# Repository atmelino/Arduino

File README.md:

# Arduino

Contents:

<h2>MPPT Arduino</h2>

http://www.home-automation-community.com/arduino-low-power-how-to-run-atmega328p-for-a-year-on-coin-cell-battery/

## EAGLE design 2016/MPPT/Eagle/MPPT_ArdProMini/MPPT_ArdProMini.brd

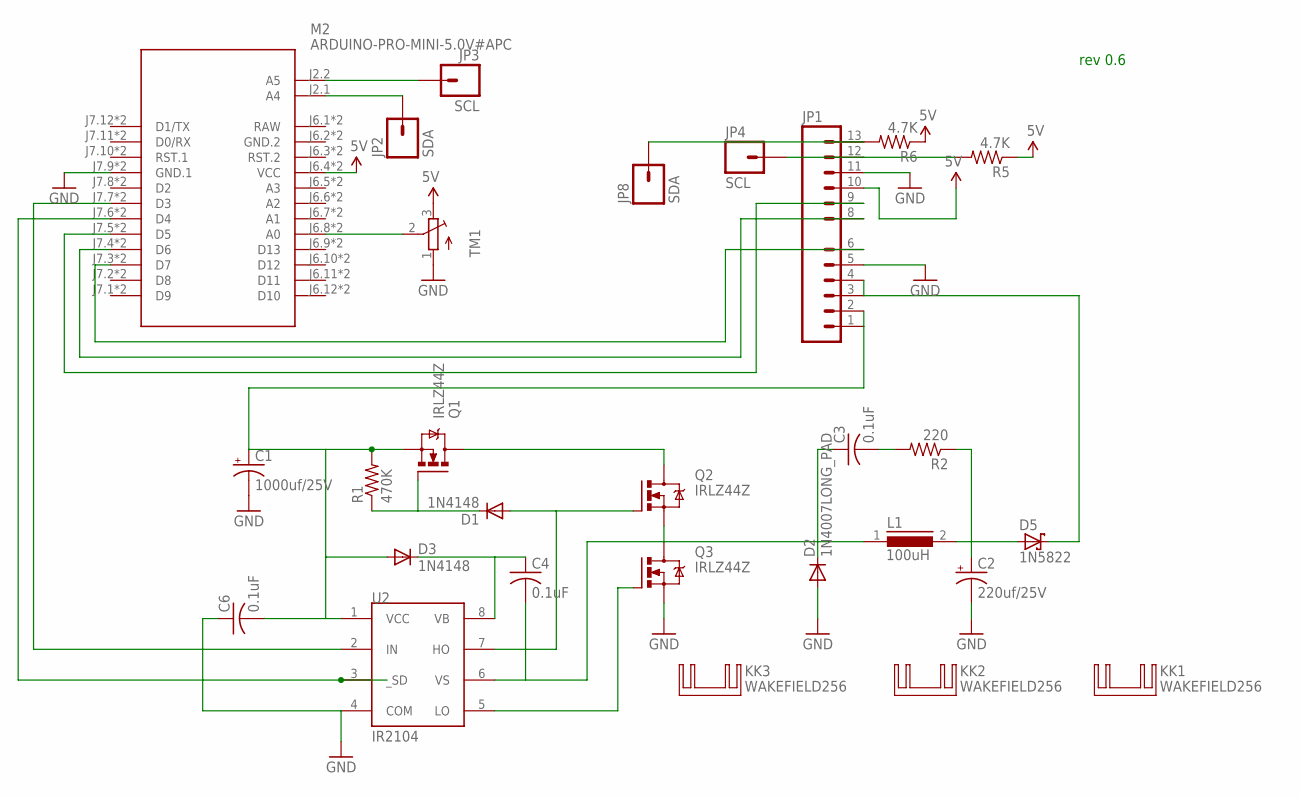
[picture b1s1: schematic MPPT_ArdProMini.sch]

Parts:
C1: 1000uf/25V; CPOL-RADIAL-1000UF-25V-KIT
C2: 220uf/25V; CPOL-RADIAL-1000UF-25V-KIT
C3: 0.1uF; C025-030X050
C4: 0.1uF; C050-030X075
C6: 0.1uF; C075-042X103
D1, D3: 1N4148; DO35-10
D2: 1N4007LONG_PAD; DO35-7
D5: 1N5822; DO201T15
JP1: M06_PLUS_06MPPT; M06_PLUS_06_MPPT
JP2, JP8: SDA; 1X01_OCT
JP3, JP4: SCL; 1X01_OCT
KK1, KK2, KK3: WAKEFIELD256; WAKEFIELD265
L1: 100uH; SFT830D
M2: ARDUINO-PRO-MINI-5.0V#APC; ARDUINO-PRO-MINI_EXTRAPADS
Q1, Q2, Q3: IRLZ44Z; TO220V
R1: 470K; 0204/7
R2: 220; 0204/7
R5, R6: 4.7K; 0204/7
TM1: TRIMPOT; TRIM-3386U
U2: IR2104; DIL08

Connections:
5V: JP1.10, M2.J6.4 (VCC), M2.J6.4_LONG (VCC), R5.1, R6.1, TM1.3 (E)
GND: C1.-, C2.-, C6.1, D2.A, JP1.5, JP1.11, M2.J7.9 (GND.1), M2.J7.9_LONG (GND.1), Q3.S, TM1.1 (A), U2.4 (COM)
GND.2: M2.J6.2 (GND.2), M2.J6.2_LONG (GND.2)
unnamed: M2.J6.8 (A0), M2.J6.8_LONG (A0), TM1.2 (S)
unnamed: JP1.12, JP4.1, R5.2
unnamed: Q3.G, U2.5 (LO)
unnamed: D1.C, Q1.G, R1.1
unnamed: JP1.9, M2.J7.5 (D5), M2.J7.5_LONG (D5)
unnamed: D5.C, JP1.3, JP1.4
unnamed: Q1.D, Q2.D
unnamed: JP1.8, M2.J7.4 (D6), M2.J7.4_LONG (D6)
unnamed: JP1.6, M2.J7.3 (D7), M2.J7.3_LONG (D7)
unnamed: C3.2, R2.2
unnamed: JP2.1, M2.J2.1 (A4)
unnamed: C3.1, C4.2, D2.C, L1.1, Q2.S, Q3.D, U2.6 (VS)
unnamed: C2.+, D5.A, L1.2, R2.1
unnamed: JP3.1, M2.J2.2 (A5)
unnamed: M2.J7.7 (D3), M2.J7.7_LONG (D3), U2.2 (IN)
unnamed: M2.J7.6 (D4), M2.J7.6_LONG (D4), U2.3 (_SD)
unnamed: D1.A, Q2.G, U2.7 (HO)
RAW: M2.J6.1 (RAW), M2.J6.1_LONG (RAW)
SDA: JP1.13, JP8.1, R6.2
VB: C4.1, D3.C, U2.8 (VB)
VCC: C1.+, C6.2, D3.A, JP1.1, JP1.2, Q1.S, R1.2, U2.1 (VCC)

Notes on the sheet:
rev 0.6

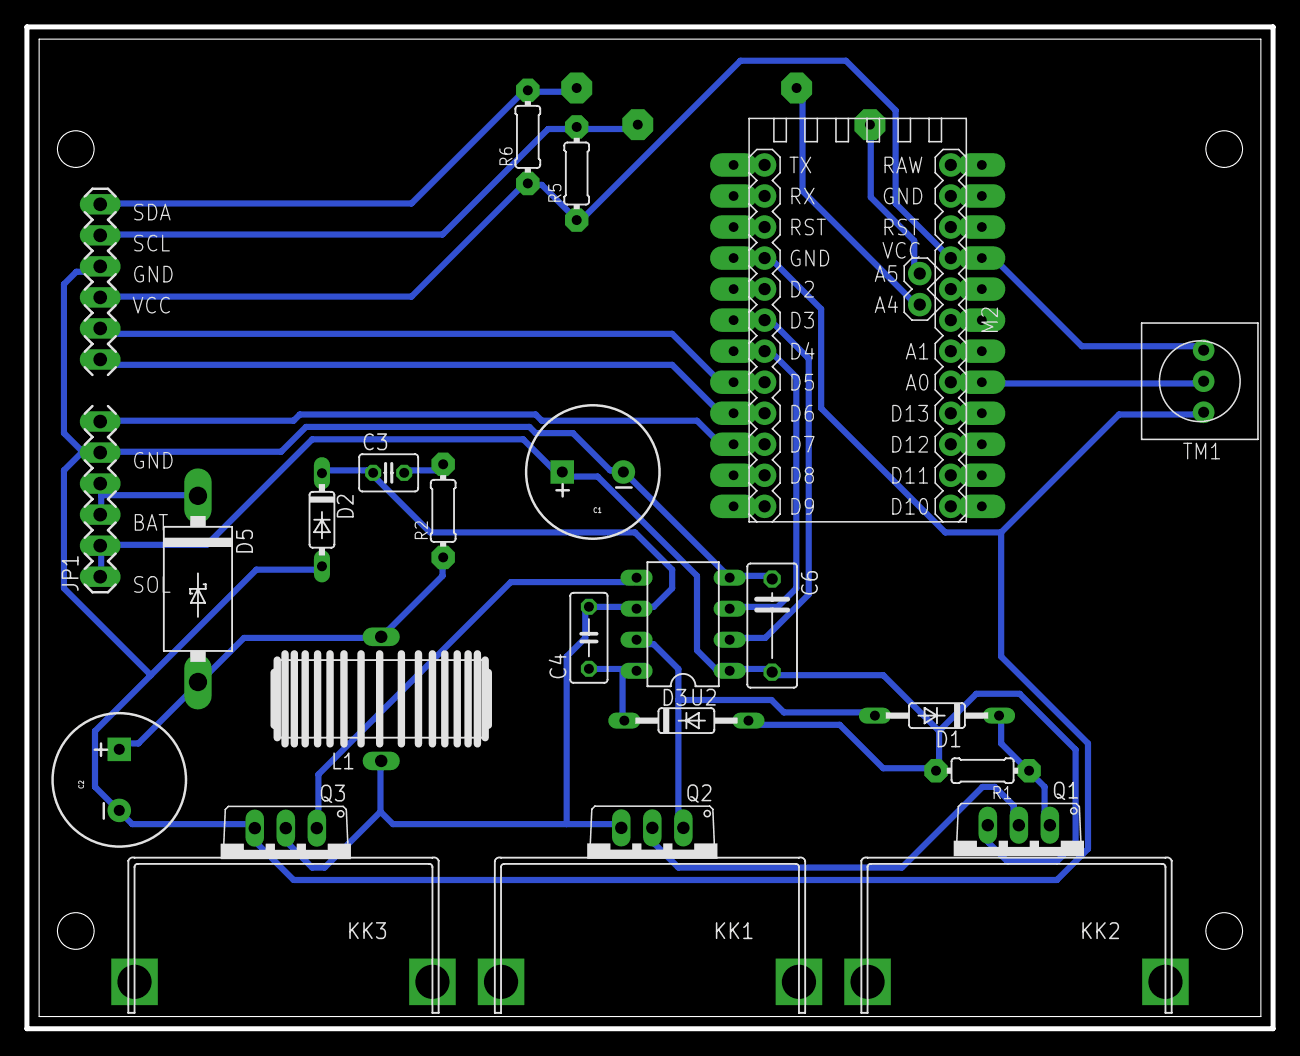
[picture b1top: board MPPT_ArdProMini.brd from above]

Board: 2 copper layers, 102.0 x 82.0 mm, 28 parts (0 on the bottom side), 24 nets.

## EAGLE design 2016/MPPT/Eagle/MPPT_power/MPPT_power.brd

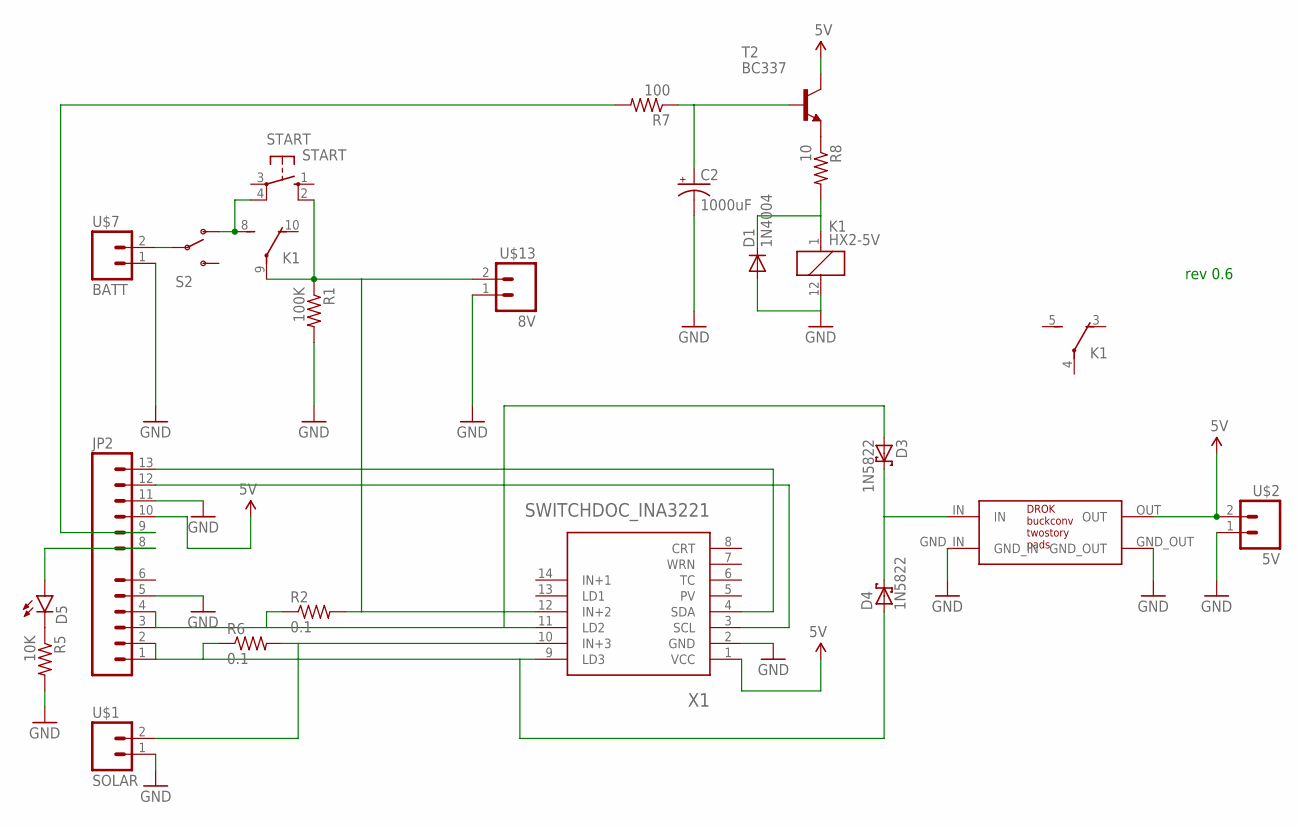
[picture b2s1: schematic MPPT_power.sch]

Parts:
C2: 1000uF; CPOL-RADIAL-1000UF-25V
D1: 1N4004; DO41-10
D3, D4: 1N5822; DO201T15
D5: LED5MM
JP2: M06_PLUS_06MPPT; M06_PLUS_06_MPPT
K1: HX2-5V; HX
R1: 100K; 0204/7
R2, R6: 0.1; 0204/7_PHAT_PAD
R5: 10K; 0204/7
R7: 100; 0204/7
R8: 10; 0204/7
S2: SWITCH-SPDT; SWITCH-SPDT_0.15_INCH
START: START; B3F-10XX
T2: BC337; TO92
U$1: SOLAR; W237-132
U$2: 5V; W237-132
U$3: DROK_BUCKCONV_TWOSTORY_PADS
U$7: BATT; W237-132
U$13: 8V; W237-132
X1: SWITCHDOC_INA3221; SWITCHDOC_INA3221_NODRILL

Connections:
5V: JP2.10, T2.3 (C), U$2.2, U$3.OUT, X1.1 (VCC)
GND: C2.-, D1.A, JP2.5, JP2.11, K1.12 (2), R1.2, R5.2, U$1.1, U$2.1, U$3.GND_IN, U$3.GND_OUT, U$7.1, U$13.1, X1.2 (GND)
unnamed: K1.9, R1.1, R2.2, START.2 (S1), U$13.2, X1.12 (IN+2)
unnamed: D3.C, D4.C, U$3.IN
unnamed: D5.K (C), R5.1
unnamed: D5.A, JP2.8
unnamed: S2.2, U$7.2
unnamed: R6.2, U$1.2, X1.10 (IN+3)
unnamed: R8.1, T2.1 (E)
unnamed: JP2.9, R7.2
unnamed: K1.8 (S), S2.1 (O), START.4 (P1)
unnamed: C2.+, R7.1, T2.2 (B)
unnamed: JP2.13, X1.4 (SDA)
unnamed: JP2.12, X1.3 (SCL)
unnamed: D1.C, K1.1, R8.2
unnamed: D3.A, JP2.3, JP2.4, R2.1, X1.11 (LD2)
unnamed: D4.A, JP2.1, JP2.2, R6.1, X1.9 (LD3)

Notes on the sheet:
rev 0.6

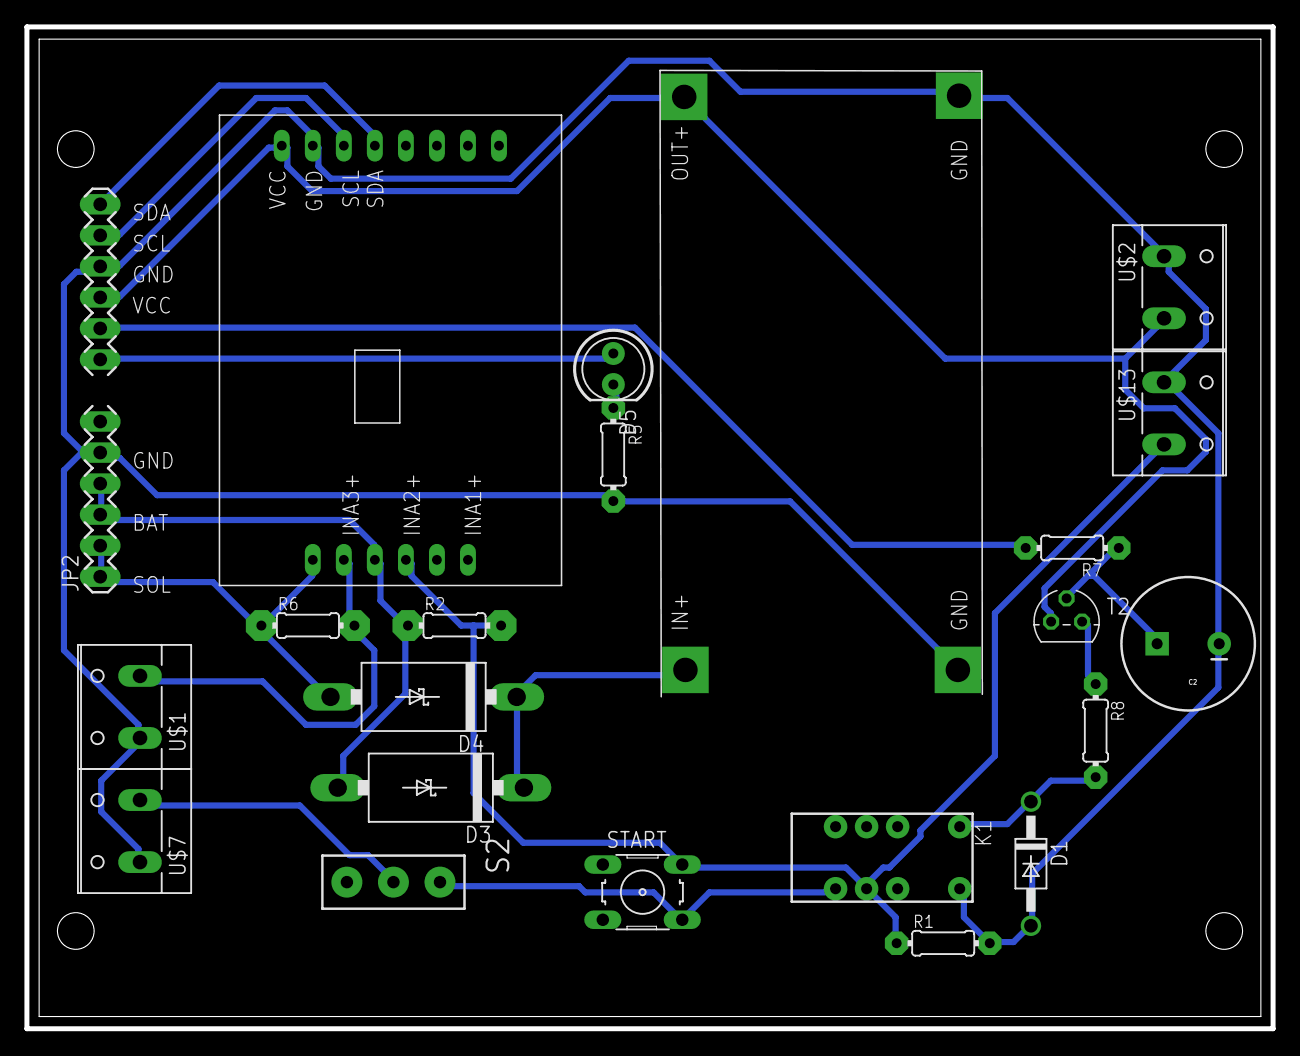
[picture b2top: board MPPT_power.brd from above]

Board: 2 copper layers, 102.0 x 82.0 mm, 22 parts (0 on the bottom side), 17 nets.

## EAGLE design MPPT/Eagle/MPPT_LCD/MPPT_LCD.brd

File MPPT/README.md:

<h2>MPPT Arduino</h2>

Arduino code for Maximum Power Point Tracker project

<a href="https://hackaday.io/project/10671-arduino-mppt-solar-charge-controller">https://hackaday.io/project/10671-arduino-mppt-solar-charge-controller</a>

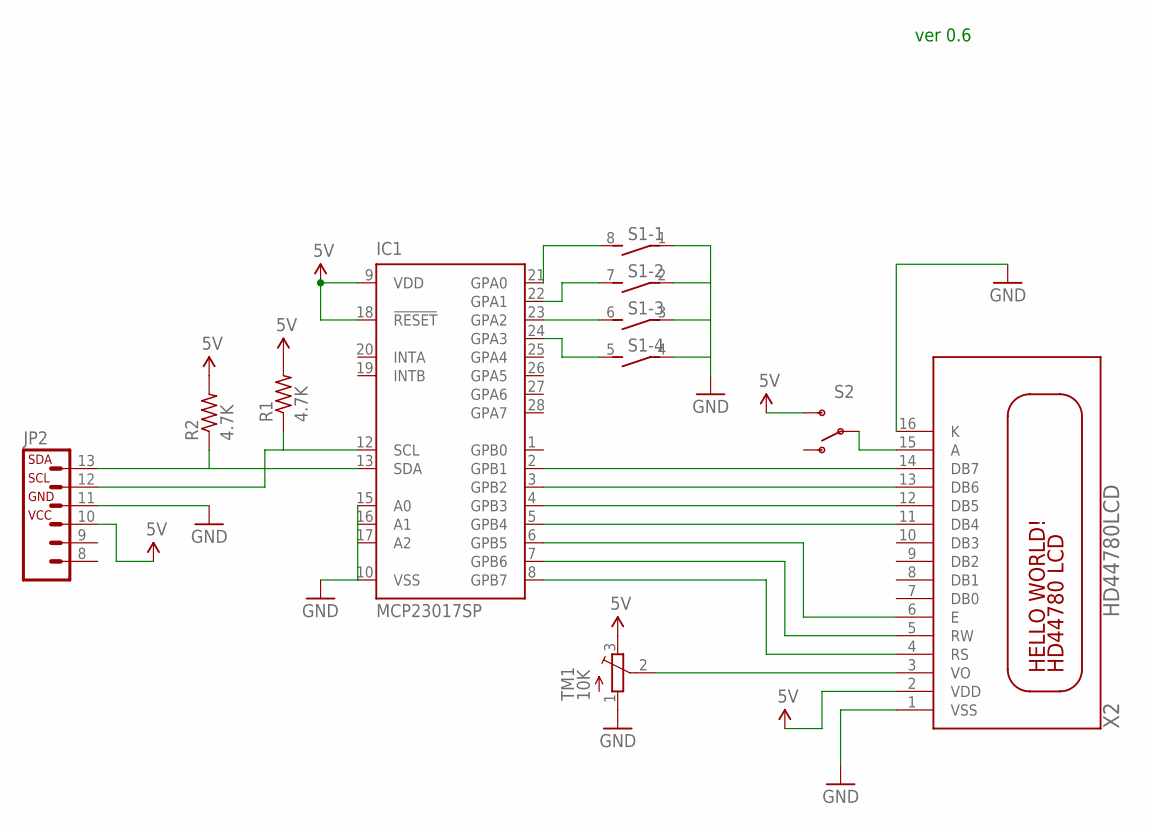
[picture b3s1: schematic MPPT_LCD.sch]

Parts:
IC1: MCP23017SP; DIL28-3
JP2: M06_MPPT_DATA
R1, R2: 4.7K; 0207/10
S1: DIP04S
S2: SWITCH-SPDTPTH; SWITCH-SPDT
TM1: 10K; TRIM-3386U
X2: HD44780LCD; LCD_40_04

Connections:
5V: IC1.9 (VDD), IC1.18 (!RESET), JP2.10, R1.2, R2.2, S2.3 (S), TM1.3 (E), X2.2 (VDD)
GND: IC1.10 (VSS), IC1.15 (A0), IC1.16 (A1), IC1.17 (A2), JP2.11, S1.1, S1.2 (1), S1.3 (1), S1.4 (1), TM1.1 (A), X2.1 (VSS), X2.16 (K)
unnamed: TM1.2 (S), X2.3 (VO)
unnamed: IC1.21 (GPA0), S1.8 (2)
unnamed: IC1.2 (GPB1), X2.14 (DB7)
unnamed: IC1.3 (GPB2), X2.13 (DB6)
unnamed: IC1.4 (GPB3), X2.12 (DB5)
unnamed: IC1.5 (GPB4), X2.11 (DB4)
unnamed: IC1.6 (GPB5), X2.6 (E)
unnamed: IC1.7 (GPB6), X2.5 (RW)
unnamed: IC1.8 (GPB7), X2.4 (RS)
unnamed: IC1.13 (SDA), JP2.13, R2.1
unnamed: IC1.12 (SCL), JP2.12, R1.1
unnamed: IC1.22 (GPA1), S1.7 (2)
unnamed: IC1.23 (GPA2), S1.6 (2)
unnamed: IC1.24 (GPA3), S1.5 (2)
unnamed: S2.2, X2.15 (A)

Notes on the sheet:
ver 0.6

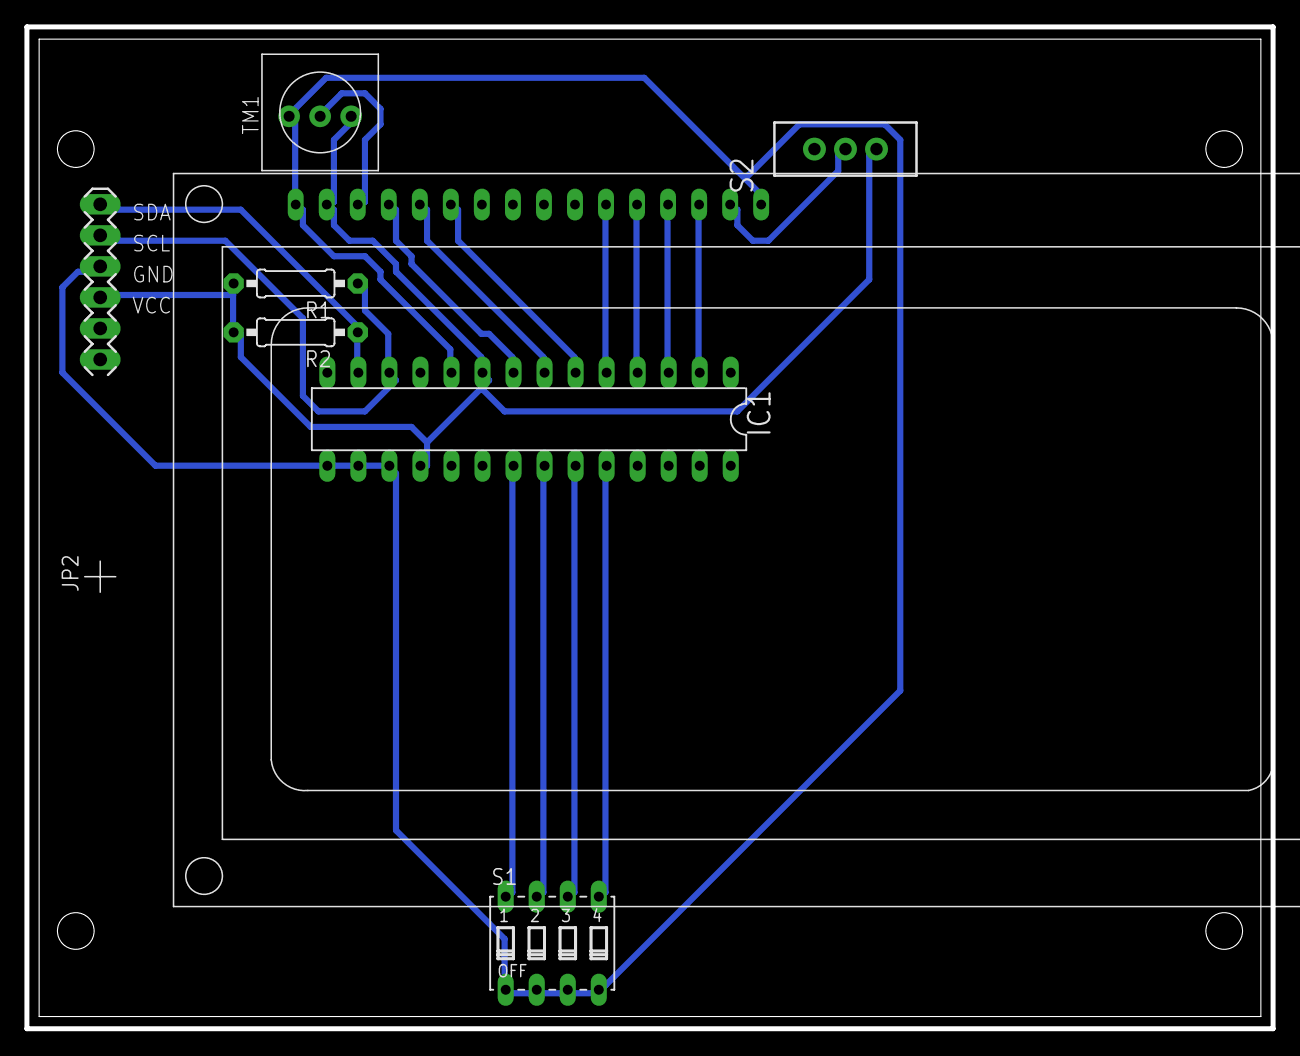
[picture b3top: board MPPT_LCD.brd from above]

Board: 2 copper layers, 102.0 x 82.0 mm, 8 parts (0 on the bottom side), 17 nets.

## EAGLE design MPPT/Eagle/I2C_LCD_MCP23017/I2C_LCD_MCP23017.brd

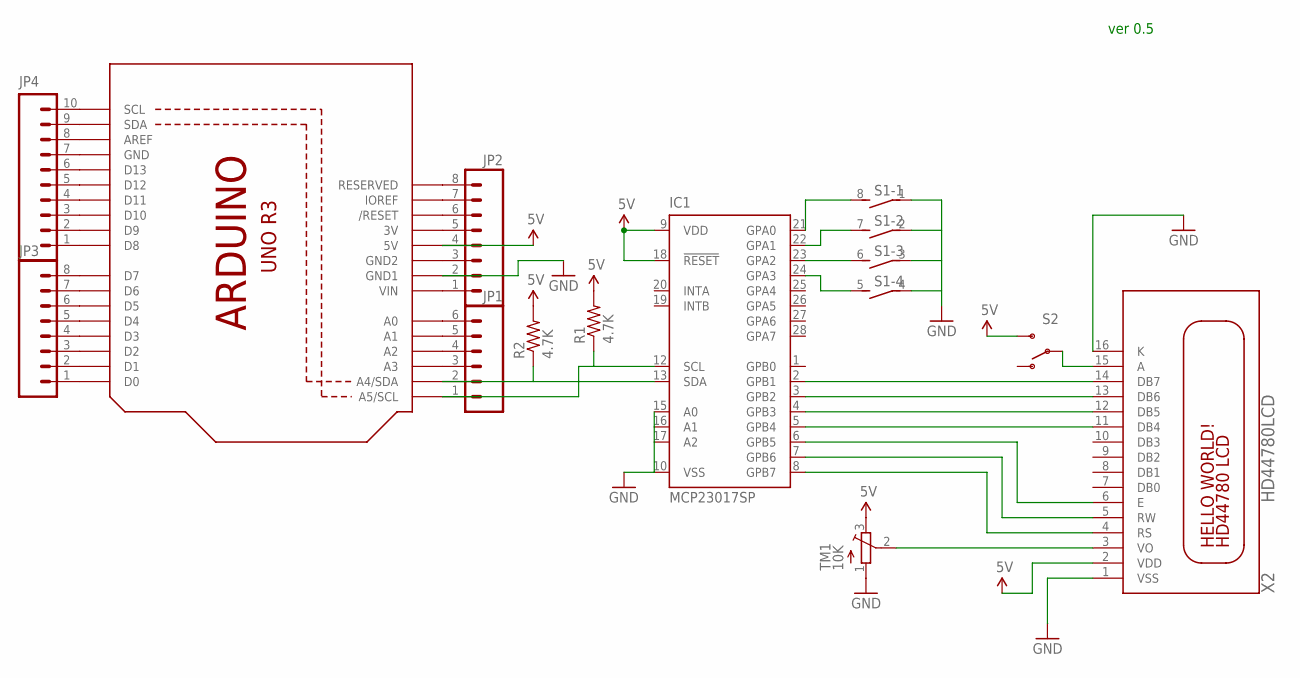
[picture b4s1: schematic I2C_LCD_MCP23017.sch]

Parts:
IC1: MCP23017SP; DIL28-3
JP1: M06LONGPADS; 1X06_LONGPADS
JP2, JP3: M08LONGPADS; 1X08_LONGPADS
JP4: M10LONGPADS; 1X10_LONGPADS
R1, R2: 4.7K; 0207/10
S1: DIP04S
S2: SWITCH-SPDTPTH; SWITCH-SPDT
TM1: 10K; TRIM-3386U
U1: ARDUINOR3LONGHEADERATBOTTOM; ARDUINOR3-BPLACE_TURNED
X2: HD44780LCD; LCD_40_04

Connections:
5V: IC1.9 (VDD), IC1.18 (!RESET), JP2.4, R1.2, R2.2, S2.3 (S), TM1.3 (E), U1.5V, X2.2 (VDD)
GND: IC1.10 (VSS), IC1.15 (A0), IC1.16 (A1), IC1.17 (A2), JP2.2, S1.1, S1.2 (1), S1.3 (1), S1.4 (1), TM1.1 (A), U1.GND1, X2.1 (VSS), X2.16 (K)
unnamed: JP4.7, U1.GND
unnamed: TM1.2 (S), X2.3 (VO)
unnamed: IC1.21 (GPA0), S1.8 (2)
unnamed: IC1.2 (GPB1), X2.14 (DB7)
unnamed: IC1.3 (GPB2), X2.13 (DB6)
unnamed: IC1.4 (GPB3), X2.12 (DB5)
unnamed: IC1.5 (GPB4), X2.11 (DB4)
unnamed: IC1.6 (GPB5), X2.6 (E)
unnamed: IC1.7 (GPB6), X2.5 (RW)
unnamed: IC1.8 (GPB7), X2.4 (RS)
unnamed: IC1.13 (SDA), JP1.2, R2.1, U1.A4 (A4/SDA)
unnamed: IC1.12 (SCL), JP1.1, R1.1, U1.A5 (A5/SCL)
unnamed: JP3.4, U1.D3
unnamed: JP1.3, U1.A3
unnamed: JP1.4, U1.A2
unnamed: JP1.5, U1.A1
unnamed: JP1.6, U1.A0
unnamed: JP2.1, U1.VIN
unnamed: IC1.22 (GPA1), S1.7 (2)
unnamed: JP2.3, U1.GND2
unnamed: IC1.23 (GPA2), S1.6 (2)
unnamed: JP2.5, U1.3V
unnamed: JP2.6, U1.RESET (/RESET)
unnamed: JP2.7, U1.IOREF
unnamed: JP2.8, U1.RESERVED
unnamed: JP3.1, U1.D0
unnamed: JP3.2, U1.D1
unnamed: JP3.3, U1.D2
unnamed: JP3.5, U1.D4
unnamed: JP3.6, U1.D5
unnamed: JP3.7, U1.D6
unnamed: JP3.8, U1.D7
unnamed: JP4.1, U1.D8
unnamed: JP4.2, U1.D9
unnamed: JP4.3, U1.D10
unnamed: JP4.4, U1.D11
unnamed: JP4.5, U1.D12
unnamed: JP4.6, U1.D13
unnamed: IC1.24 (GPA3), S1.5 (2)
unnamed: JP4.8, U1.AREF
unnamed: JP4.9, U1.SDA
unnamed: JP4.10, U1.SCL
unnamed: S2.2, X2.15 (A)

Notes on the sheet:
ver 0.5

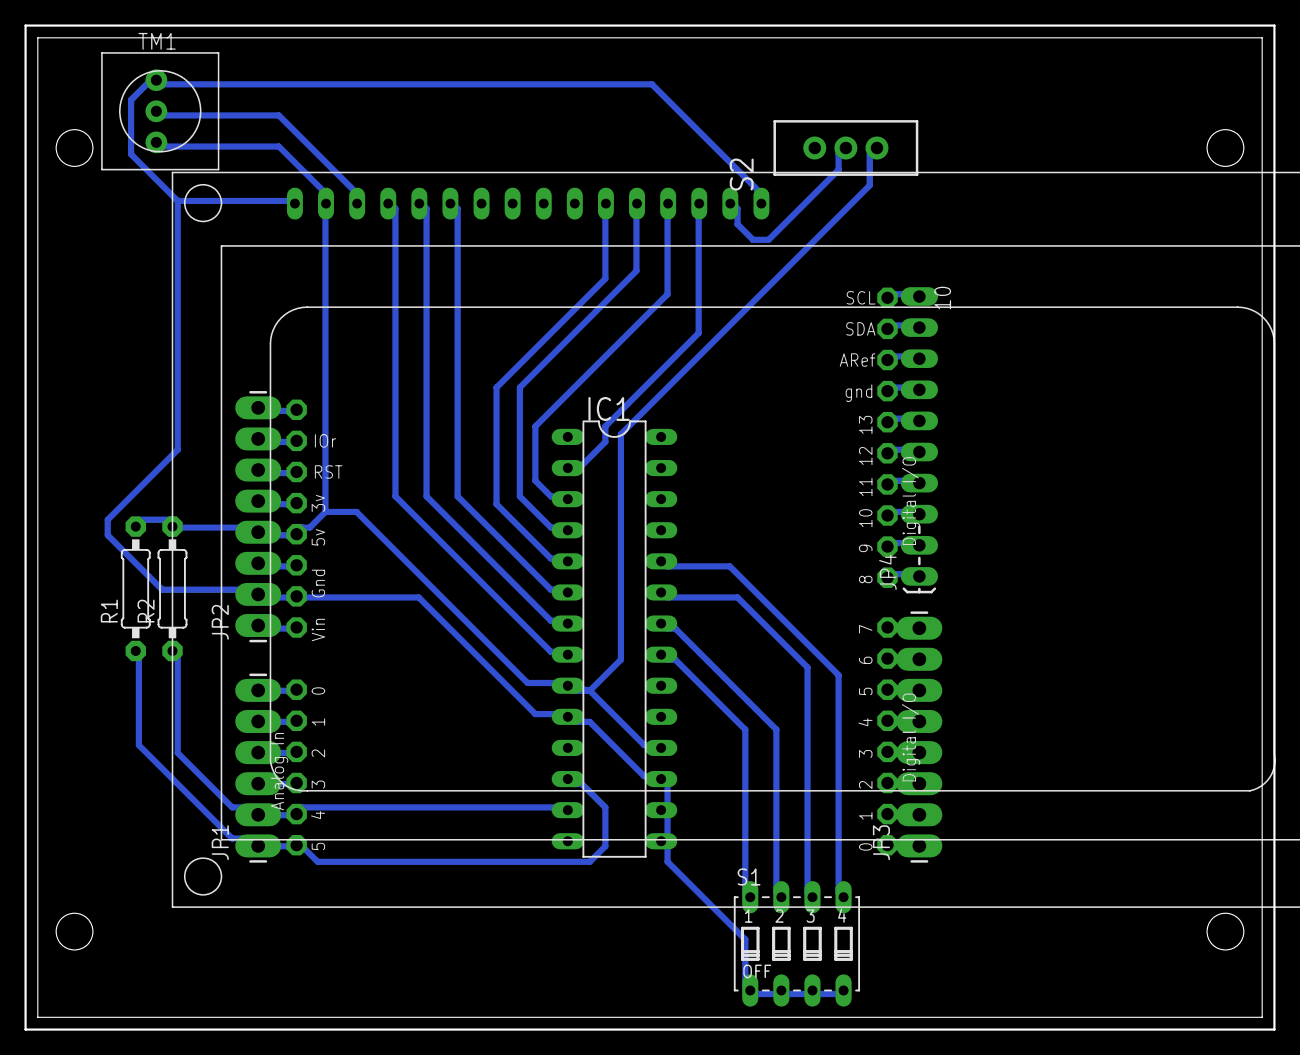
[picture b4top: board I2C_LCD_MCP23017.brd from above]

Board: 2 copper layers, 102.0 x 82.0 mm, 12 parts (0 on the bottom side), 45 nets.

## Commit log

2016-04-23 readme
2016-04-23 initial MPPT commit
2016-04-23 move network sensor into Arduino
2016-04-23 move tempHumid into Arduino
2016-04-23 git history before move
2016-04-29 power save functions
2016-05-12 relay function
2016-05-19 relay
2016-05-19 reorganize and Eagle files
2016-05-19 readme images
2016-05-20 power save no floating pins
2016-05-22 PWM library
2016-05-29 pin headers
2016-05-29 over 8.4 volt delay too long error
2016-06-01 set potentiometer pin as input
2016-06-10 5V supply pin
2016-07-10 I2C communication
2016-07-10 SDL library
2016-07-10 libraries
2016-07-25 serial Arduino to Pi
2016-07-25 simpler PWM change method
2016-08-24 send PWM vakue through serial
2016-08-26 DIP switches
2016-08-30 set default PWM for serial to 200
2016-09-05 send new PWM value via JSON
2016-09-23 power cycle pi if not running
2016-09-23 print statements
2019-01-19 start 2019 version
2019-01-19 2019 version
2019-01-22 JSON for serial comm
2019-01-23 PWM set
2019-01-23 print line
2019-01-24 another PWM library
2019-01-25 reorganize PWM
2019-01-25 PWM test
2019-01-25 IP address
2019-01-26 initial pulse width
2019-01-28 rename
2019-01-28 comments
2019-01-28 voltages
2019-01-30 move MPPT to separate repository
2019-01-31 cleanup

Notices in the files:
parts and their libraries:
SparkFun-Capacitors: Licensing: Creative Commons ShareAlike 4.0 International - https://creativecommons.org/licenses/by-sa/4.0
